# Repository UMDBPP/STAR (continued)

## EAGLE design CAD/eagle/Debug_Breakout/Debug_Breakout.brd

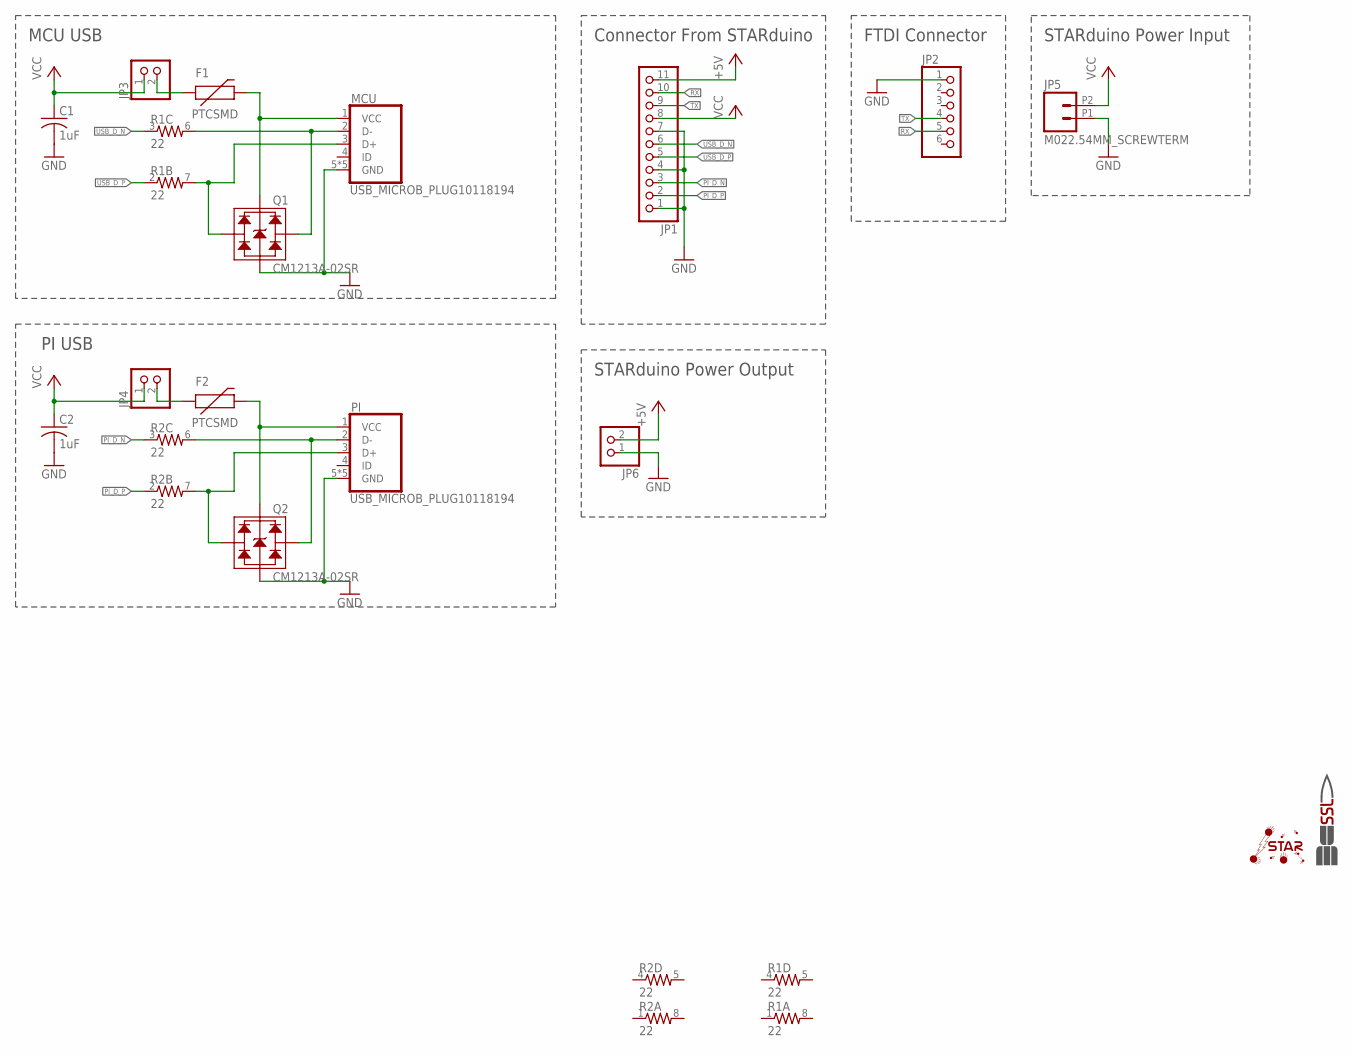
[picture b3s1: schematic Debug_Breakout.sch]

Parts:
C1, C2: 1uF; C0603
F1, F2: PTCSMD; PTC-1206
JP1: PINHD-1X11; 1X11
JP2: PINHD-1X6; 1X06
JP3, JP4, JP6: PINHD-1X2; 1X02
JP5: M022.54MM_SCREWTERM; 1X02_2.54_SCREWTERM
MCU: USB_MICROB_PLUG10118194; MICRO-B-10118194
PI: USB_MICROB_PLUG10118194; MICRO-B-10118194
Q1, Q2: CM1213A-02SR; SOT143-4
R1, R2: 22; 0603-ARV
U$1: SSL.3IN_SILK; SSL_SILK_.3IN
U$2: STAR; STAR_.3IN

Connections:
+5V: JP1.11, JP6.2
GND: C1.2, C2.2, JP1.1, JP1.4, JP1.7, JP2.1, JP5.P1 (1), JP6.1, MCU.5 (GND), MCU.S1 (GND), MCU.S2 (GND), MCU.S3 (GND), MCU.S4 (GND), PI.5 (GND), PI.S1 (GND), PI.S2 (GND), PI.S3 (GND), PI.S4 (GND), Q1.P$1 (GND), Q2.P$1 (GND)
MCU_D_N: MCU.2 (D-), Q1.P$3 (CH2), R1.6 (2)
MCU_D_P: MCU.3 (D+), Q1.P$2 (CH1), R1.7 (2)
unnamed: F2.2, PI.1 (VCC), Q2.P$4 (VCC)
unnamed: F1.2, MCU.1 (VCC), Q1.P$4 (VCC)
unnamed: F2.1, JP4.2
unnamed: F1.1, JP3.2
PICONN_D_N: PI.2 (D-), Q2.P$3 (CH2), R2.6 (2)
PICONN_D_P: PI.3 (D+), Q2.P$2 (CH1), R2.7 (2)
PI_D_N: JP1.3, R2.3 (1)
PI_D_P: JP1.2, R2.2 (1)
RX: JP1.10, JP2.5
TX: JP1.9, JP2.4
USB_D_N: JP1.6, R1.3 (1)
USB_D_P: JP1.5, R1.2 (1)
VCC: C1.1, C2.1, JP1.8, JP3.1, JP4.1, JP5.P2 (2)

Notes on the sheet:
MCU USB
PI USB
Connector From STARduino
STARduino Power Output
STARduino Power Input
FTDI Connector

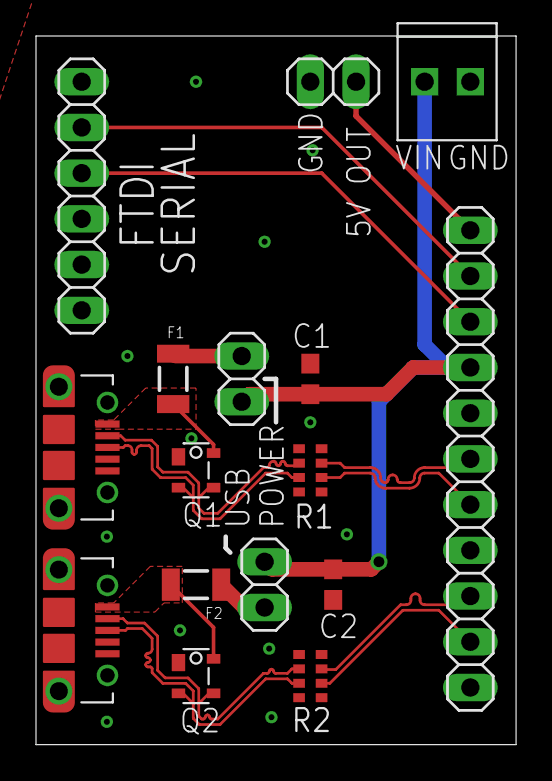
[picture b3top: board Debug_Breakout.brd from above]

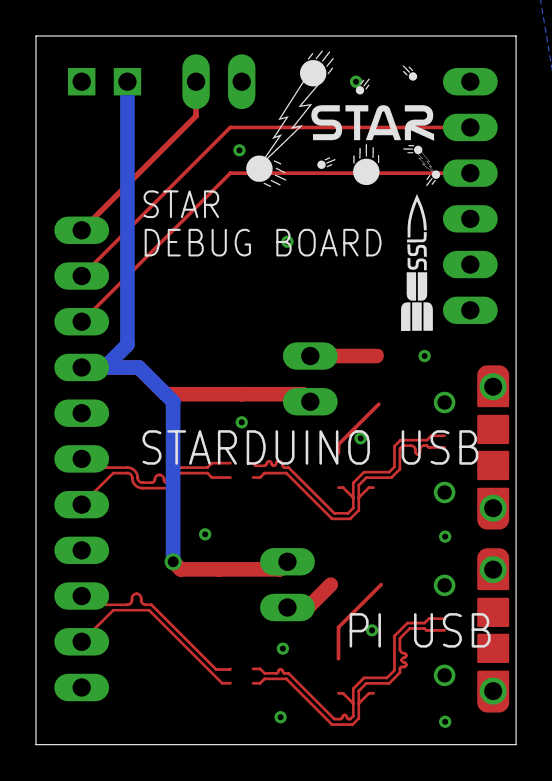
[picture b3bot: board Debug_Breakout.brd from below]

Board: 2 copper layers, 26.7 x 39.4 mm, 18 parts (2 on the bottom side), 17 nets.

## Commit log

2017-02-03 updated directory structure
2017-02-03 mcu block
2017-02-03 updated libraries and power input
2017-02-09 Beginnings of sensor block
2017-02-10 Added High G accelerometer
2017-02-10 Removed lock file.
2017-02-10 Added Makefile and made script edits
2017-02-10 Added Mechanical Drawings
2017-02-11 Added real time clock, edited UART header to include common ground line.
2017-02-11 Finished adding sensors
2017-02-12 Finished my part - added IMU, Micro SD, Onboard Flash.
2017-02-12 aesthetic and spacing for schematic
2017-02-14 added LED driver, second UART line
2017-02-16 LED Driver no longer UFBGA
2017-02-16 Added enable line to LED driver
2017-02-16 Added Motor Driver
    Added motor driver chip and hacked mutliplexer; will upgrade to real
    multiplexer.
2017-02-16 Added Driver Chip to Library
    Added driver chip to library
2017-02-16 Removed Hacked Motor PWM Driver/Multiplexer
    Removed hacked motor PWM driver/multiplexer
2017-02-17 updated CAD for new footprint
2017-02-18 Added sensor carrier board schematic
2017-02-18 Finished sensor board layout. Please check.
2017-02-19 Added Multiplexer
    Added multiplexer for motor driver and assosciated level-shifting
    circuitry.
2017-02-19 Renumbered Resistors
    Renumbered resistors in motor driver and multiplexer blocks to maintain
    consecutive numbering.
2017-02-19 Did a bunch of stuff: Swapped to larger onboard flash (128 MB), Added debug UART, Removed pressure senaor and replaced with header to external board, moved each comm interface to use only one SERCOM.
2017-02-20 Updated Motor Driver Configuration
    Made motor driver decay mode configurable via the multiplexer
    Changed current sense resistors to 1.05 ohm for more granular control
    over current limiting
    Added a pull-up on nENBL so the output stage will be disabled until
    explicitly commanded otherwise
    Renumbered resistors accordingly
2017-02-20 Added resistor.lbr
2017-02-20 Updated Motor Driver Library
    Updated motor driver library to include more parts.
2017-02-21 Fixed dumb mistake on external sensor board, screw holes are now right distance apart. Rerouted around hole placement and verfied that DRC was still okay.
2017-02-22 added gitignore, updated schematic for analog reference and LED driver PWM
2017-02-22 Stuff
2017-02-22 Added libraries
2017-02-22 Finalish CAD for STR
2017-02-22 Renamed some nets, reorganized a bit, removed unnecessary headers
2017-02-22 Updated Renderings
2017-02-22 Added i2c buffer to CM_IC
2017-02-22 Fixed gitignore.
2017-02-22 Added I2C buffer to STARduino for external board.
2017-02-22 Added Inventor Libraries
2017-02-22 Added external power switching.
2017-02-22 Added I2C buffer to external sensor board.
2017-02-23 Power supply shit
2017-02-23 removed bad nets on MCU and removed all greek letters
2017-02-23 Added J30J connectors
2017-02-27 Pi things
2017-02-28 More Pi/Pi CSI things
2017-02-28 layout file now exists
2017-02-28 more layout things, MDM adjustments
2017-02-28 Altered external sensor board to use J30J-25 connector instead of headers. Board is final aside from logos.
2017-03-01 removed garbage
2017-03-01 Cleaned up some symbols
2017-03-02 Schematic updates
2017-03-02 Reorganization and initial shop drawings
2017-03-03 Update Makefile
2017-03-03 Create PiInfo
2017-03-06 Layout and schematic progress
2017-03-06 Fixed STEPFREQ schematic bug.
2017-03-07 initial commit of STARduino code. have tested messaging and confirmed that it works, in the process of testing command sequence loading and execution. initial version of utility to create command seq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
2017-03-07 added additional comments to functions, added get pkt length function to ccsds_utilities, added additional init text messages, updated RecordCmdSeq (still not fully working, ocassionally receives ran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
2017-03-07 fix stuff
2017-03-07 Updated Drawings and Solar Sheild
2017-03-07 Added coding guidelines for STARduino
2017-03-07 Clarified variable naming guideline; added macro naming rule.
2017-03-08 fixed command loading and execution, now working. also redid command file creation tool in matlab because python was stealing my bytes
2017-03-08 Added bias voltage route to external board
2017-03-08 Better differential pair routing.
2017-03-08 Board routing
2017-03-08 Fixed Arduino fuckery
2017-03-08 added UT for new Queue library
2017-03-08 Changed variable naming guideline; local variables now recommended to have trailing underscore.
2017-03-08 updated class commenting to match styleguide
2017-03-08 updated comments in UT_Queue to match style guide
2017-03-08 layout stuff
2017-03-08 routing
2017-03-08 attempted to stub arduino SD libraries, still testing the stubbed out version because having issues with available(). added test files with known errors for unit tsting
2017-03-09 fixed stubbed SD class, added UT for SD class, fixed UT for load_sd
2017-03-09 updated Readme for current tests, added (currently not working) test for load_cmdseq
2017-03-09 Began work on pressure sensor library. Realized I specced an inadequate sensor. Specced a better sensor (in the same family). Changed external sensor board to compensate.
2017-03-09 Removed unneeded board label.
2017-03-09 Revised SC-70 land pattern.
2017-03-09 Package stuff
2017-03-09 Added header for honeywell pressure sensor.
2017-03-09 Fixed types; added supersampling provision in pressure sensor header.
2017-03-09 Commented Honeywell header, added provision for non-default constructor. Added power sensor library to read analog power sensors. Classes are identical at this time; might use polymorphism to reduce 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
2017-03-09 Removed reference to no longer used current sensor.
2017-03-10 Additional coding guideline for global variables.
2017-03-10 updated command logic to allow a place for filter commands based on where they're received from, added loigc which compiles commands read across multiple reads, added file interaction commands (need 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
2017-03-10 moved UT out of STARduino folder because arduino IDE is dumb and is trying to compile it, minor fixes to make software compile
2017-03-10 fixed write file command
2017-03-10 layout progress
2017-03-13 Final layouts and gerbers
2017-03-13 Added STEP files and updated drawings
2017-03-13 Removed Lock Files
2017-03-14 cycle timing now working, reading commands across cycles now working, FileInfo and FileChksum commands now responding (filesize and checksum appear wrong)
2017-03-14 moved addStrtoTlm to ccsds_utilities, added additional comments, fixed minor errors
2017-03-14 trying to get message logging to work
2017-03-16 resolved remaining issues with message logging causing resets, added helper function for getting file from Idx, implemented sendFile command
2017-03-16 Few tweaks to sensor headers but slow progress. Added RasPi Arch instal scripts.
2017-03-16 Actually add rpi Arch build script
2017-03-17 Update PiInfo
2017-03-22 Updated Shop Drawings
2017-03-27 Final STARduino stuff+ASM guides
2017-03-28 Added a bunch of STARduino sensor code.
2017-03-28 More sensor code.
2017-03-29 PowerSensors cpp done
    The quick brown fox jumped over the lazy dog. I mean, the .cpp file for
    the powersensors was created and some edits to the .h file.
2017-03-30 Power Sensors 30 Mar
    moved some #defines to the header file, fixed input defintions and
    changed variables to reflect nomencalture guidelines. Made voltage and
    current classes default pins A0 and A4
2017-03-30 I hate lock files
2017-03-30 Hole call outs added to some shop drawings
2017-03-30 Hole call outs added to more shop drawings
2017-03-31 Power Sensors 30 Mar Again
    Added max numSamples and zero protection, updated nomenclature
2017-04-07 Photo Loopchanges
2017-04-07 Adding Photo Capture Loop
2017-04-12 Deficiencies.txt added
2017-04-13 More stuff
2017-04-27 Added TCA9535 Driver
    Added driver for the TCA9535 multiplexer. It has basic documenation, but
    more would probably be useful.
2017-04-27 Cleane up TCA9535 Code
    Added documenation for the TCA9535 driver for standards compliance.
2017-04-27 Updated CAD to adjust for CTU Modifications
2017-05-15 updated deficiencies.txt
2017-05-22 Minor changes to CAD drawings
2017-05-23 Adjusted some STARduino things
2017-05-23 DRV Driver
    Initial commit of DRV code; very incomplete.
2017-05-24 Multiplexer Pinout Change
    Small change to multiplexer layout for increased sense-making.
2017-05-24 Beginning rework of expternal sensor board.
2017-05-25 Finished External Sensor Board reroute.
2017-05-26 Minor changes to external board upon review.
2017-05-26 Updated Bolt Holes on RSX Deck
2017-05-26 Updtaed STEP Files and Shop Drawings for RSX Deck and Slide Rods
2017-05-26 STARduino progress. De-stupified 28V bias
2017-05-26 Fixed SERCOMS.
2017-05-26 Finished schematic changes
2017-05-27 New starduino routing done
2017-05-27 Change layout version number
2017-05-27 Added debug breakout schematic
2017-05-27 Fixed STARduino DRC
2017-05-27 begin routing debug board.
2017-05-27 Finished STAR debug board.
2017-05-28 Motor holder change and resulting bolt changes
2017-05-28 Base plate shop drawing changes
2017-05-28 pi camera mount fix
2017-05-29 Solar Sheild Changes and Tube holder bolt adjustments
2017-05-29 STARduino minor mechanical adjustments
2017-05-29 ESB traces and breakout 15 pin labels
2017-05-30 CTU RSX plate step file and shop drawing
2017-06-01 STARduino solder paste adjustments
2017-06-01 New Brackets, with changed baseplate and solar shield
2017-06-02 CAM files
2017-06-02 Motor Driver Update
    Motor drive complete except for PWM code
2017-06-04 Added STARduino mounting holes to base plate
2017-06-06 PWM Code for Motor Driver
    Added code to operate PWM system to drive stepper motor. Probably
    contains bugs.
2017-06-09 Working Motor Driver
    Motor driver now works and doesn't nuke the USB controller.
2017-06-11 misc CAD Updates, added some fasteners
2017-06-16 fasteners
2017-06-16 Added ADXL code
    Still needs comments.
2017-06-16 Refactored code to agree with Arduino's arcane build environment. Also fixed several small bugs. Code now compiles!
2017-06-16 Added EZGPIO. Also nuked starduino.ino for time being; current test ino does work.
2017-06-16 Added EZGPIO helper functions.
2017-06-16 Made inputs volatile.
2017-06-16 Added foil and mesh cutting patterns
2017-06-16 Update test sketch. EZGPIO functions not working; bare registers are.
2017-06-17 CAD with fasteners
2017-06-17 CAD with fasteners and no lockfiles
2017-06-18 TCA I2C Bugfix
    Bugfix for TCA I2C code. I2C still doesn't work, but I caught this, so I
    figured I'd fix it.
2017-06-18 exploded drawings
2017-07-04 misc drawings for manual
2017-07-04 more manual stuff
2017-07-22 Updated deficiencies list
2017-07-23 Further updated deficiencies list
2017-08-02 Added sensor test sketch for STARDuino
2017-08-04 Updated sensor libraries
    Lots of bug fixes
2017-08-04 Added begin method to ADXL
    Added beign() method to take care of ADXL power-on tasks. Can't put it
    in the constructor because I2C calls cannot be made in the constructor.
2017-08-04 Updated STARDuino hardware deficiencies list
2017-08-04 Fligh code (hopefully)
2017-08-04 Added magnetometer
2017-08-05 Disabled flash CS
2017-08-05 Fixed silly typo
2017-08-05 Updated hardware deficiencies list
2017-08-05 Updated timing for magentometer
